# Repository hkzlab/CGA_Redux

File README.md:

# Color Graphics Adapter - Redux

## Introduction

The Color Graphics Adapter (**CGA**) Redux board is a more or less faithful clone of the original IBM CGA, based on the original schematics.

Since revision 0.2 of this board, **You can decide to build it with the "new" or "old" style composite output**, giving you slightly different colours.

Have a look [HERE](https://int10h.org/blog/2015/08/8088-mph-final-old-vs-new-cga-gory-details/) for a blog post that discusses the difference in regard to the famous **8088MPH** demo!

### Disclaimer

I take NO responsibility for what happens if you decide to build and use this card. Your computer might crash, catch fire or be destroyed in other nasty ways.
You're encourauged to take what you deem fit from this, and use it in your projects!

### Functionalities

✅ means I tested the functionality and it works, ❌ means I tested the functionality and found issues, ? means that the functionality has yet to be tested.

* [✅] Digital display in text mode, 40 columns
* [✅] Digital display in text mode, 80 columns
* [✅] Composite display in text mode, 40 columns
* [✅] Composite display in text mode, 80 columns
* [✅] Graphics mode in digital
* [✅] Graphics mode in composite
* [✅] Run CheckIt video test
* [✅] 8088MPH Demo
* [?] Light pen input

## Bill of Materials

| Component         | Qty | Type / Value        |
| ----------------- | --- | ------------------- |
| **TODO**          |     |                     |

### Character ROM

This board needs a character ROM to work. I would advise to search for a dump of IBM P/N 5788005, concatenate it four times and burn it on a 27C256 EPROM.

### Component substitutions

* U4,U5 and U101 should all be 'S174s, but I had only 'LS174 available. The board looks to be working without issues anyway
* U50-U57 are all 120ns DRAMs in my original board. I had only 150ns chips for this build, and they worked fine
* U9,U10 are 74153 chips. I tried to replace them with 74LS153 chips by Texas Instruments with good results. **Needs some testing with colored screens**
* U50-U57 can be substituted by 41256 / 4164 DRAMs like the M5K4164 or HM4864P (the additional address lines are grounded). **Tested with HM4864P**

## Support

If you wish to support me in building new hardware and software for old machines, [throw a few euros in my direction via Ko-Fi](https://ko-fi.com/hkzlab) ☕!

### 💰 Selling these boards 💰

I you want to contact me about selling this project, you can reach me via email at `0hkzUNDERSCOREprojects6ATposteoDOTnet` after properly fixing the email address by removing the digits and replacing the uppercase words with the proper characters.

**Contacts via other channels will be ignored**, as it means you did not read this document thoroughly.

"Collaborations" will boil down to the following:

- If you wish to produce and share this project at a loss or at cost, go for it. I am only asking for attribution and to let me know via email.
- If you want to do it for profit, let's discuss it. I'll probably settle for a rough 5% of the profit. Importing components is getting more expensive by the day, so this will contribute to me making future projects available for free.
- I will NOT do customer assistance for you or your customers. This is a hobby, not my job.

If this is not ok for you, you're cordially invited to go bother someone else :)

Authorized sellers will be listed in this README. If you find someone selling my boards without being listed here, it means they're stealing other people's work.

## Known issues

### Rev 0

* The Composite video out has an inverted connection for that type of footprint. (fixed in rev 0.1)
* Silkscreen for U28 says 74LS10, but it's actually an 74S10 on an original board (fixed in rev 0.1)
* traces that connect the edge to the power planes for 5V and GND are a bit too thin for my taste (fixed in rev 0.1)

## TODO

* ???

## Credits

Thanks to [Sergey Kiselev](https://github.com/skiselev) for his symbol/footprint library!

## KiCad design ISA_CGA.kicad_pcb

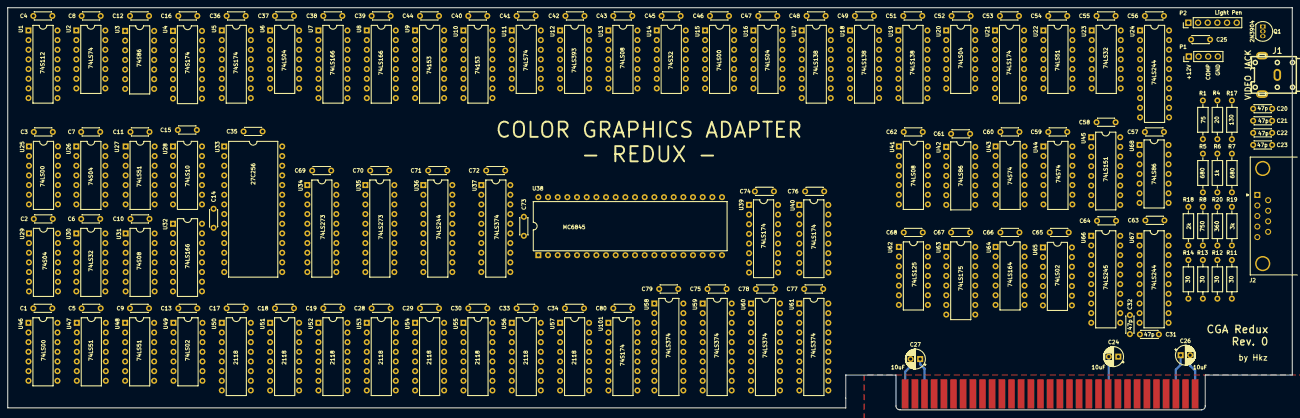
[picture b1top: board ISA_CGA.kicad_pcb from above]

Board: 4 copper layers, 337.6 x 105.7 mm, 168 parts (0 on the bottom side), 300 nets.

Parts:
C1, C2, C3, C4, C5, C6, C7, C8, C9, C10, C11, C12, C13, C14, C15, C16, C17, C18, C19, C25, C28, C29, C30, C33, C34, C35, C36, C37, C38, C39, C40, C41, C42, C43, C44, C45, C46, C47, C48, C49, C51, C52, C53, C54, C55, C56, C57, C58, C59, C60, C61, C62, C63, C64, C65, C66, C67, C68, C69, C70, C71, C72, C73, C74, C75, C76, C77, C78, C79, C80: 100nF; C_Disc_D4.3mm_W1.9mm_P5.00mm
C20, C21, C22, C23, C31, C32: 47p; C_Disc_D4.3mm_W1.9mm_P5.00mm
C24, C26, C27: 10uF; CP_Radial_D5.0mm_P2.50mm
J1: VIDEO JACK; rca_yellow
J2: RGBI Output; DSUB-9_Female_Horizontal_P2.77x2.84mm_EdgePinOffset7.70mm_H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
P1: 1X4 BERG; PinHeader_1x04_P2.54mm_Vertical
P2: 1X6 BERG; PinHeader_1x06_P2.54mm_Vertical
P5: Bus_ISA_8bit; Conn_Edge_PCB_ISA8
Q1: 2N3904; TO-92_Inline
R1: 75; R_Axial_DIN0207_L6.3mm_D2.5mm_P10.16mm_Horizontal
R4: 20; R_Axial_DIN0207_L6.3mm_D2.5mm_P10.16mm_Horizontal
R5, R7: 680; R_Axial_DIN0207_L6.3mm_D2.5mm_P10.16mm_Horizontal
R6: 1k; R_Axial_DIN0207_L6.3mm_D2.5mm_P10.16mm_Horizontal
R8: 750; R_Axial_DIN0207_L6.3mm_D2.5mm_P10.16mm_Horizontal
R11, R12, R13, R14: 30; R_Axial_DIN0207_L6.3mm_D2.5mm_P10.16mm_Horizontal
R17: 130; R_Axial_DIN0207_L6.3mm_D2.5mm_P10.16mm_Horizontal
R18: 2k; R_Axial_DIN0207_L6.3mm_D2.5mm_P10.16mm_Horizontal
R19: 3k; R_Axial_DIN0207_L6.3mm_D2.5mm_P10.16mm_Horizontal
R20: 360; R_Axial_DIN0207_L6.3mm_D2.5mm_P10.16mm_Horizontal
U1: 74S112; DIP-16_W7.62mm
U2, U11: 74LS74; DIP-14_W7.62mm
U3: 74S86; DIP-14_W7.62mm
U4, U5, U101: 74S174; DIP-16_W7.62mm
U6, U16, U20: 74LS04; DIP-14_W7.62mm
U7, U8, U32: 74LS166; DIP-16_W7.62mm
U9, U10: 74153; DIP-16_W7.62mm
U12: 74LS393; DIP-14_W7.62mm
U13, U41: 74LS08; DIP-14_W7.62mm
U14: 74S32; DIP-14_W7.62mm
U15, U25, U46: 74LS00; DIP-14_W7.62mm
U17, U18, U19: 74LS138; DIP-16_W7.62mm
U21, U39, U40: 74LS174; DIP-16_W7.62mm
U22, U27, U47, U48: 74LS51; DIP-14_W7.62mm
U23, U30: 74LS32; DIP-14_W7.62mm
U24, U36, U67: 74LS244; DIP-20_W7.62mm
U26, U29: 74S04; DIP-14_W7.62mm
U28: 74LS10; DIP-14_W7.62mm
U31: 74S08; DIP-14_W7.62mm
U33: 27C256; DIP-28_W15.24mm
U34, U35: 74LS273; DIP-20_W7.62mm
U37, U58, U59, U60, U61: 74LS374; DIP-20_W7.62mm
U38: MC6845; DIP-40_W15.24mm
U42, U68: 74LS86; DIP-14_W7.62mm
U43, U44: 74S74; DIP-14_W7.62mm
U45: 74LS151; DIP-16_W7.62mm
U49, U65: 74LS02; DIP-14_W7.62mm
U50, U51, U52, U53, U54, U55, U56, U57: 2118; DIP-16_W7.62mm
U62: 74LS125; DIP-14_W7.62mm
U63: 74LS175; DIP-16_W7.62mm
U64: 74LS164; DIP-14_W7.62mm
U66: 74LS245; DIP-20_W7.62mm

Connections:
3.58_MHZ: U5.12, U5.14, U43.12
14_MHZ: U1.1, U1.13, U4.9, U5.9, U6.13, U26.12, U43.11, U44.3
+12V: C24.1, C25.2, P1.1, P2.6, P5.9
/CGA 1/6/RAM-A0: U50.5, U51.5, U52.5, U53.5, U54.5, U55.5, U56.5, U57.5, U58.2, U59.2, U60.2, U61.2
/CGA 1/6/RAM-A1: U50.7, U51.7, U52.7, U53.7, U54.7, U55.7, U56.7, U57.7, U58.5, U59.5, U60.5, U61.5
/CGA 1/6/RAM-A2: U50.6, U51.6, U52.6, U53.6, U54.6, U55.6, U56.6, U57.6, U58.6, U59.6, U60.6, U61.6
/CGA 1/6/RAM-A3: U50.12, U51.12, U52.12, U53.12, U54.12, U55.12, U56.12, U57.12, U58.9, U59.9, U60.9, U61.9
/CGA 1/6/RAM-A4: U50.11, U51.11, U52.11, U53.11, U54.11, U55.11, U56.11, U57.11, U58.12, U59.12, U60.12, U61.12
/CGA 1/6/RAM-A5: U50.10, U51.10, U52.10, U53.10, U54.10, U55.10, U56.10, U57.10, U59.15, U60.15, U61.15, U62.3
/CGA 1/6/RAM-A6: U50.13, U51.13, U52.13, U53.13, U54.13, U55.13, U56.13, U57.13, U58.15, U59.16, U60.16, U61.16
/CGA 2/6/AT0: U7.2, U10.6, U35.19
/CGA 2/6/AT1: U8.2, U9.10, U35.16
/CGA 2/6/AT2: U7.3, U9.6, U35.15
/CGA 2/6/AT3: U8.3, U10.10, U35.12
/CGA 2/6/AT4: U7.4, U10.5, U35.9
/CGA 2/6/AT5: U8.4, U9.11, U35.6
/CGA 2/6/AT6: U7.5, U9.5, U35.5
/CGA 2/6/CC0: U7.10, U33.7, U34.19
/CGA 2/6/CC1: U8.10, U33.6, U34.16
/CGA 2/6/CC2: U7.11, U33.5, U34.15
/CGA 2/6/CC3: U8.11, U33.4, U34.12
/CGA 2/6/CC4: U7.12, U33.3, U34.9
/CGA 2/6/CC5: U8.12, U33.25, U34.6
/CGA 2/6/CC6: U7.14, U33.24, U34.5
/CGA 2/6/CC7: U8.14, U33.21, U34.2
/CGA 5/6/BLUE: U43.8, U45.3
/CGA 5/6/CYAN: U44.6, U45.1
/CGA 5/6/GREEN: U44.8, U45.2
/CGA 5/6/MAGENTA: U44.9, U45.14
/CGA 5/6/RED: U44.5, U44.12, U45.15
/CGA 5/6/YELLOW_BURST: U43.9, U44.2, U45.13
/CGA 6/6/DB0: P5.40, U66.2
/CGA 6/6/DB1: P5.39, U66.3
/CGA 6/6/DB2: P5.38, U66.4
/CGA 6/6/DB3: P5.37, U66.5
/CGA 6/6/DB4: P5.36, U66.6
/CGA 6/6/DB5: P5.35, U66.7
/CGA 6/6/DB6: P5.34, U66.8
/CGA 6/6/DB7: P5.33, U66.9
/CGA 6/6/OSC: P5.30, U26.13
/CGA 6/6/~SMEMR: P5.12, U42.12
A0: U13.6, U17.1, U38.24, U61.14
A1: P5.61, U17.2, U60.3
A2: P5.60, U17.3, U60.4
A3: P5.59, U17.6, U30.1, U60.7
A4: P5.58, U18.1, U60.8
A5: P5.57, U18.5, U60.13
A6: P5.56, U18.2, U60.14
A7: P5.55, U18.3, U60.17
A8: P5.54, U41.2, U61.3
A9: P5.53, U41.1, U61.4
A10: P5.52, U61.7
A11: P5.51, U61.8
A12: P5.50, U61.13
A13: P5.49, U61.17
A15: P5.47, U19.1
A16: P5.46, U19.2
A17: P5.45, U19.3
A18: P5.44, U19.4
A19: P5.43, U19.6
AEN: P5.42, U14.9, U18.4
ALPHA_DOTS: U14.6, U22.11
AT7: U8.5, U28.11, U31.9, U35.2
AT_LATCH: U35.11, U47.8
B: U45.11, U67.6, U67.15, U101.7
BACKGROUND_I: U10.12, U39.12
B_OUT: C22.1, R13.2, U67.14
C0: U7.13, U9.12, U22.2, U23.2, U48.2
C1: U8.13, U9.4, U23.1, U48.4
CAS_CC: U3.11, U25.10, U29.13
CC_LATCH: U25.8, U34.11
CHG_DOTS: U13.13, U32.13
COLOR_SEL: U22.4, U39.15
COMP_VID: J1.1, P1.3, R4.1
CURSOR: U20.1, U38.19
D0: U24.3, U36.2, U37.2, U38.33, U39.3, U40.3, U66.18
D1: U24.5, U36.4, U37.5, U38.32, U39.4, U40.4, U66.17
D2: U24.7, U36.6, U37.6, U38.31, U39.6, U40.6, U66.16
D3: U24.9, U36.8, U37.9, U38.30, U39.11, U40.11, U66.15
D4: U36.11, U37.12, U38.29, U39.13, U40.13, U66.14
D5: U36.13, U37.15, U38.28, U39.14, U40.14, U66.13
D6: U36.15, U37.16, U38.27, U66.12
D7: U36.17, U37.19, U38.26, U66.11
DATA_GATE: U13.8, U66.19
DISPEN: U20.3, U38.18
DOT_CLOCK: U7.7, U8.7, U25.2, U26.11, U27.8, U32.7
E: U11.9, U38.23
ENABLE_BLINK: U16.5, U28.10, U40.15
G: U24.4, U67.4, U68.1, U101.5
GND: C1.1, C2.1, C3.1, C4.1, C5.1, C6.1, C7.1, C8.1, C9.1, C10.1, C11.1, C12.1, C13.1, C14.1, C15.1, C16.1, C17.1, C18.1, C19.1, C20.2, C21.2, C22.2, C23.2, C24.2, C25.1, C26.2, C27.2, C28.1, C29.1, C30.1, C31.2, C32.2, C33.1, C34.1, C35.1, C36.1, C37.1, C38.1, C39.1, C40.1, C41.1, C42.1, C43.1, C44.1, C45.1, C46.1, C47.1, C48.1, C49.1, C51.1, C52.1, C53.1, C54.1, C55.1, C56.1, C57.1, C58.1, C59.1, C60.1, C61.1, C62.1, C63.1, C64.1, C65.1, C66.1, C67.1, C68.1, C69.1, C70.1, C71.1, C72.1, C73.1, C74.1, C75.1, C76.1, C77.1, C78.1, C79.1, C80.1, J1.2, J2.0, J2.1, J2.2, P1.4, P2.4, P5.1, P5.10, P5.31, R1.1, R17.2, U1.8, U2.7, U3.7, U4.8, U5.8, U6.7, U7.1, U7.6, U7.8, U8.1, U8.6, U8.8, U9.8, U10.8, U11.7, U12.7, U13.7, U14.7, U15.7, U16.7, U17.8, U18.8, U19.8, U20.7, U21.8, U22.7, U23.7, U24.1, U24.10, U25.7, U26.7, U27.7, U28.7, U29.7, U30.7, U31.7, U32.1, U32.6, U32.8, U33.2, U33.14, U33.22, U33.23, U33.26, U33.27, U34.10, U35.10, U36.10, U37.10, U38.1, U39.8, U40.8, U41.7, U42.7, U42.13, U43.7, U44.7, U45.4, U45.7, U45.8, U46.7, U47.7, U48.7, U49.7, U50.8, U51.8, U52.8, U53.8, U54.8, U55.8, U56.8, U57.8, U58.10, U59.10, U60.10, U61.10, U62.7, U62.10, U62.13, U63.8, U64.7, U65.7, U66.10, U67.1, U67.10, U67.19, U68.7, U101.8
GRPH: U16.11, U22.13, U23.13, U40.5, U47.1, U48.12
G_OUT: C21.1, R12.2, U67.16
HCLK: U5.7, U6.9, U21.9, U27.3
HRES: U16.13, U27.2, U27.9, U30.5, U40.2, U47.3, U49.3
HSYNC: U21.6, U38.39
HSYNC_DLY: U21.7, U43.1, U64.9, U65.6
HSYNC_OUT: C32.1, J2.8, U67.9
I: U24.6, U67.8, U101.10
IO_CLOCK: P5.20, U11.11
IO_READY: P5.41, U62.6
I_OUT: C23.1, R14.2, U67.12
LCLK: U6.2, U27.5, U43.3, U64.8
LPEN_STR: U11.5, U24.15, U38.3
MD0: U34.18, U35.18, U36.18, U37.3, U57.2, U57.14
MD1: U34.17, U35.17, U36.16, U37.4, U56.2, U56.14
MD2: U34.14, U35.14, U36.14, U37.7, U55.2, U55.14
MD3: U34.13, U35.13, U36.12, U37.8, U54.2, U54.14
MD4: U34.8, U35.8, U36.9, U37.13, U53.2, U53.14
MD5: U34.7, U35.7, U36.7, U37.14, U52.2, U52.14
MD6: U34.4, U35.4, U36.5, U37.17, U51.2, U51.14
MD7: U34.3, U35.3, U36.3, U37.18, U50.2, U50.14
MUX_A: U9.14, U10.14, U23.8
MUX_B: U9.2, U10.2, U23.11
unnamed: J2.3, R11.1
unnamed: J2.4, R12.1
unnamed: J2.5, R13.1
unnamed: J2.6, R14.1
unnamed: P5.62, U13.4, U13.5
unnamed: Q1.1, R1.2, R4.2
unnamed: Q1.2, R5.1, R6.1, R7.1, R8.1, R17.1, R18.1, R19.1, R20.2
unnamed: R5.2, U24.18
unnamed: R6.2, U24.16
unnamed: R7.2, U24.14
unnamed: R8.2, U24.12
unnamed: R18.2, U67.3
unnamed: R19.2, U67.5
unnamed: U1.5, U46.5, U46.13
unnamed: U1.6, U46.2, U46.10
unnamed: U1.9, U3.9
unnamed: U1.12, U26.4
unnamed: U2.6, U28.4, U47.2
unnamed: U2.10, U29.6
unnamed: U2.5, U2.12
unnamed: U2.4, U2.9, U2.13
unnamed: U3.1, U5.5, U6.11
unnamed: U3.3, U30.10
unnamed: U3.8, U31.1
unnamed: U3.12, U4.5, U4.6, U49.2
unnamed: U4.7, U4.11
unnamed: U4.15, U5.3
unnamed: U5.10, U6.5
unnamed: U5.13, U6.4
unnamed: U5.15, U6.3
unnamed: U10.7, U101.6
unnamed: U10.9, U101.11
unnamed: U10.11, U31.8
unnamed: U11.1, U17.12
unnamed: U11.3, U29.4
unnamed: U11.4, U17.11
unnamed: U11.12, U11.13, U15.8, U16.1
unnamed: U12.2, U12.12, U65.13
unnamed: U13.1, U15.3
unnamed: U13.9, U29.10
unnamed: U13.11, U14.4
unnamed: U13.12, U14.3
unnamed: U14.1, U28.8
unnamed: U14.5, U49.13
unnamed: U14.8, U41.4
unnamed: U14.11, U65.8
unnamed: U14.12, U20.10
unnamed: U14.13, U43.5
unnamed: U15.2, U21.5, U21.14
unnamed: U15.4, U15.5, U43.2, U64.13
unnamed: U15.6, U42.9
unnamed: U15.11, U28.1
unnamed: U15.12, U16.3, U40.12
unnamed: U16.2, U17.4, U65.3
unnamed: U16.4, U22.12, U23.5
unnamed: U16.9, U22.3, U29.9, U40.7
unnamed: U17.5, U18.7, U30.2, U65.2
unnamed: U18.6, U41.3
unnamed: U19.5, U41.11
unnamed: U20.2, U21.3
unnamed: U20.5, U22.6
unnamed: U20.11, U64.12
unnamed: U20.12, U24.2
unnamed: U20.13, U42.6
unnamed: U21.2, U21.13
unnamed: U22.1, U23.3
unnamed: U22.8, U23.9
unnamed: U23.4, U26.8
unnamed: U23.6, U28.13
unnamed: U24.8, U45.5
unnamed: U25.1, U25.11, U48.5
unnamed: U25.9, U30.6
unnamed: U25.3, U25.12, U48.3
unnamed: U25.13, U26.10
unnamed: U26.5, U46.9, U46.12, U47.6
unnamed: U26.6, U46.1, U46.4
unnamed: U26.9, U48.6
unnamed: U28.2, U65.4
unnamed: U28.3, U29.2
unnamed: U28.5, U49.4
unnamed: U29.11, U65.1
unnamed: U29.12, U31.2
unnamed: U30.9, U49.1
unnamed: U32.2, U33.11
unnamed: U32.3, U33.12
unnamed: U32.4, U33.13
unnamed: U32.5, U33.15
unnamed: U32.10, U33.16
unnamed: U32.11, U33.17
unnamed: U32.12, U33.18
unnamed: U32.14, U33.19
unnamed: U33.20, U68.11
unnamed: U38.4, U59.3
unnamed: U38.5, U59.4
unnamed: U38.6, U59.7
unnamed: U38.7, U59.8
unnamed: U38.8, U59.13
unnamed: U38.9, U59.14
unnamed: U38.10, U59.17
unnamed: U38.11, U58.3
unnamed: U38.12, U58.4
unnamed: U38.13, U58.7
unnamed: U38.14, U58.8
unnamed: U38.15, U58.13
unnamed: U38.16, U48.9
unnamed: U41.6, U66.1
unnamed: U41.8, U42.4, U67.13
unnamed: U41.9, U63.2, U63.5
unnamed: U41.10, U63.14
unnamed: U5.6, U42.3
unnamed: U42.5, U63.9, U64.4, U67.11
unnamed: U42.8, U64.1
unnamed: U42.10, U64.6
unnamed: U45.9, U68.6
unnamed: U45.10, U68.3
unnamed: U48.8, U49.8, U49.9
unnamed: U49.10, U58.14
unnamed: U62.8, U62.12
unnamed: U63.10, U63.13
unnamed: U63.7, U63.12
unnamed: U65.10, U68.2, U68.5
unnamed: U68.8, U68.12
unnamed: U9.7, U101.3
unnamed: U9.9, U101.4
unnamed: U101.12, U101.14
OVERSCAN_B: U10.3, U39.2
OVERSCAN_G: U9.13, U39.5
OVERSCAN_I: U10.13, U39.10
OVERSCAN_R: U9.3, U39.7
Q1: U2.3, U3.4, U5.2, U5.4, U47.4, U60.11, U61.11
Q4: U3.13, U4.10, U4.13, U42.2, U68.10
Q5: U1.11, U4.12, U4.14, U26.3, U49.6
R: U67.2, U67.17, U68.4, U101.2
RA0: U33.10, U38.38, U48.1
RA1: U33.9, U38.37
RA2: U33.8, U38.36
RAS: U1.3, U3.6, U26.1
RESET: P5.2, U20.9, U68.13
R_OUT: C20.1, R11.2, U67.18
SEL_BLUE: U10.4, U20.6
SL: U7.15, U8.15, U32.15, U62.11
SL': U30.8, U62.9
STR: U9.1, U9.15, U10.1, U10.15, U28.12
VCC: C1.2, C2.2, C3.2, C4.2, C5.2, C6.2, C7.2, C8.2, C9.2, C10.2, C11.2, C12.2, C13.2, C14.2, C15.2, C16.2, C17.2, C18.2, C19.2, C26.1, C27.1, C28.2, C29.2, C30.2, C33.2, C34.2, C35.2, C36.2, C37.2, C38.2, C39.2, C40.2, C41.2, C42.2, C43.2, C44.2, C45.2, C46.2, C47.2, C48.2, C49.2, C51.2, C52.2, C53.2, C54.2, C55.2, C56.2, C57.2, C58.2, C59.2, C60.2, C61.2, C62.2, C63.2, C64.2, C65.2, C66.2, C67.2, C68.2, C69.2, C70.2, C71.2, C72.2, C73.2, C74.2, C75.2, C76.2, C77.2, C78.2, C79.2, C80.2, P2.5, P5.3, P5.29, Q1.3, R20.1, U1.4, U1.10, U1.14, U1.15, U1.16, U2.1, U2.14, U3.14, U4.16, U5.16, U6.14, U7.16, U8.16, U9.16, U10.16, U11.2, U11.10, U11.14, U12.14, U13.14, U14.14, U15.14, U16.14, U17.16, U18.16, U19.16, U20.14, U21.1, U21.16, U22.9, U22.14, U23.14, U24.20, U25.14, U26.14, U27.10, U27.13, U27.14, U28.14, U29.14, U30.14, U31.14, U32.16, U33.1, U33.28, U34.1, U34.20, U35.20, U36.20, U37.20, U38.20, U39.16, U40.16, U41.14, U42.14, U43.14, U44.14, U45.12, U45.16, U46.14, U47.10, U47.13, U47.14, U48.10, U48.13, U48.14, U49.14, U50.16, U51.16, U52.16, U53.16, U54.16, U55.16, U56.16, U57.16, U58.20, U59.20, U60.20, U61.20, U62.14, U63.4, U63.16, U64.2, U64.14, U65.14, U66.20, U67.20, U68.14, U101.1, U101.16
VIDEO_ENABLE: U13.2, U40.10
VSYNC: U21.11, U38.40
VSYNC_DLY: U12.1, U21.10, U24.11, U63.1, U65.5, U65.9
VSYNC_OUT: C31.1, J2.9, U67.7
XACK: U2.8, U37.11, U62.5
~7_MHZ: U5.11, U6.6, U27.1
~14_MHZ: U6.12, U27.11, U44.11, U101.9
~6845_CS: U30.3, U38.25
~BLINK: U12.11, U14.2
~BW_1: U29.8, U44.1, U44.4, U44.10, U44.13
~BW_2: U16.8, U22.5, U43.4, U43.10, U43.13
~CAS: U31.3, U50.15, U51.15, U52.15, U53.15, U54.15, U55.15, U56.15, U57.15
~CCLK: U27.6, U30.4, U38.21, U47.11
~CLR_SR: U7.9, U8.9, U13.3, U32.9, U35.1
~CPU_MEM_SEL: U2.2, U13.10, U19.7, U29.5, U30.12, U62.4
~CURSOR_BLINK: U12.6, U12.13, U49.12
~CURSOR_DLY: U21.12, U28.9, U49.11
~DISPEN: U20.4, U21.4, U24.17
~DISPEN_DLY: U15.1, U15.13, U21.15, U23.10, U23.12
~ENABLE_BLINK: U16.6, U31.10
~EN_CPU_CAS_ADDR: U46.6, U61.1
~EN_CPU_RAS_ADDR: U46.3, U60.1
~EN_CRT_CAS_ADDR: U46.11, U58.1, U62.1
~EN_CRT_RAS_ADDR: U46.8, U59.1
~GRPH: U16.10, U22.10, U47.9, U48.11
~HCLK: U6.8, U62.2
~HRES: U16.12, U27.4, U27.12, U47.5
~IOR: P5.14, U14.10, U15.9
~IOW: P5.13, U15.10, U38.22
~LCLK: U3.2, U3.5, U3.10, U4.2, U4.4, U6.1, U68.9
~LPEN_INPUT: P2.1, U29.3
~LPEN_SW: P2.3, U24.13
~MEMR: U30.13, U41.5, U41.12, U42.11
~MEMW: P5.11, U29.1, U41.13
~Q2': U4.3, U6.10, U42.1, U47.12, U49.5
~RAS: U1.2, U2.11, U26.2, U50.4, U51.4, U52.4, U53.4, U54.4, U55.4, U56.4, U57.4, U58.11, U59.11
~RD_GATE: U30.11, U37.1
~RESET: U4.1, U5.1, U38.2, U39.1, U40.1, U101.15
~RESET': U20.8, U65.11, U65.12, U101.13
~SEL_1: U17.15, U40.9
~SEL_2: U17.14, U39.9
~STATUS_SEL: U17.13, U24.19
~WE: U28.6, U36.1, U36.19, U50.3, U51.3, U52.3, U53.3, U54.3, U55.3, U56.3, U57.3

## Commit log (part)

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2021-03-08 Add empty project
2021-03-08 Begin drawing first sheet of CGA
2021-03-08 Complete a sheet
2021-03-08 Remove char from label
2021-03-09 Begin 2nd sheet
2021-03-09 More drawings of sheet 2
2021-03-09 More sheet 2
2021-03-09 More sheet 2
2021-03-09 Move some components
2021-03-09 More of sheet 2
2021-03-10 Added MK36000 symbol
2021-03-10 More sheet 2 changes
2021-03-10 Resized sheet
2021-03-10 Added power for ICs in sheet 2
2021-03-10 Begin drawing sheet 3/6
2021-03-10 More sheet 3 drawing
2021-03-10 More sheet 3
2021-03-11 Sheet 3
2021-03-11 Cleanup more sheet 3
2021-03-11 Cleanup sheet
2021-03-11 Power connection for more units
2021-03-11 more sheets
2021-03-11 More power inputs
2021-03-11 Begin sheet 4
2021-03-11 More sheet 4
2021-03-11 More CGA sheet 4
2021-03-11 Some more sheet 4
2021-03-12 Add original manual
2021-03-12 Add more of sheet 4
2021-03-13 Sheet 4
2021-03-13 Begin sheet 5
2021-03-13 More sheet 5
2021-03-14 Sheet 5
2021-03-14 More power connections for sheet 5
2021-03-14 Add some components to sheet 6
2021-03-14 More sheet 6
2021-03-14 Sheet 6
2021-03-14 Add pics and readme
2021-03-14 Replace pic with PNG
2021-03-14 Add pic
2021-03-14 Update board
2021-03-15 Fix some label types in sheet 1
2021-03-15 Fix some more label types
2021-03-19 Add missing connection to Vcc/GND for two ICs
2021-03-20 Fix one of the gates of U15 on sheet 3
2021-03-20 Fixed some duplicate units and mislabeling
2021-03-20 Fix RAM bus connections
2021-03-20 Fix some more flags and footprints
2021-03-21 Cleanup schematics a bit
2021-03-25 Update note on caps at the RGBI connector
2021-03-25 Reorganize DRAM address lines
2021-03-25 Added note on RAM chips
2021-03-28 Add note on light pen input and change the label types
2021-03-29 Add extra libraries and assign footprints
2021-03-29 Replace MK36000 with 27C256
2021-03-29 Begin preparing board
2021-03-29 Fixed some footprints
2021-04-02 Add filter caps for every IC
2021-04-02 Begin laying out ICs
2021-04-02 Laying out more components
2021-04-02 Additional layout
2021-04-02 Reorganize space between ICs
2021-04-02 More layout
2021-04-02 Reorganize layout a bit
2021-04-02 Place some more ICs
2021-04-02 Place more components
2021-04-02 place all components
2021-04-02 Add mask
2021-04-02 Close board outline
2021-04-02 Changed footprints, moving components
2021-04-02 Redone layout
2021-04-02 Route power tracks in inner layers
2021-04-02 Moved some components
2021-04-02 Add keepout areas for autorouter
2021-04-02 Added copper fill zones
2021-04-03 Fix connections in power plane
2021-04-03 Added some silkscreen
2021-04-03 Add some more silkscreen entries
2021-04-03 More silkscreen, slightly move component
2021-04-03 More silkscreen
2021-04-04 Commit PCB before importing the routed traces
2021-04-04 Imported traces
2021-04-06 Remove redundant file
2021-04-07 Fixed wrong DRAM pinout
2021-04-07 connect the two NC in DRAM to GND, so ideally 4164 and 41256 can be used
2021-04-19 Rewire 27C256 so a dump from the original MK36000 can be used unchanged
2021-04-27 Reroute tracks to edge connector
2021-04-27 Reroute backside traces to edge connector
2021-04-27 Fix back mask
2021-04-27 Reroute some tracks that were in inner layers
2021-05-25 Add some more grounding
2021-05-27 Add rev 1.0 gerbers
2021-05-28 Add fatter power traces, added gerbers for rev.0
2021-05-28 Slightly move a via
2021-06-09 Replaced RCA jack
2021-06-10 Fix power trace running below composite connector
2021-06-10 Replaced 74LS10 for U28 with 74S10
2021-06-10 Add new README
2021-06-10 Update to the README
2021-06-10 Fix missing end of sentence in README
2021-06-10 Add section on functionalities
2021-06-12 Add more positive checks to the README!
2021-06-12 Updated README with note on 8088MPH
2021-06-12 Clearup
2021-06-13 Add rev 0.1 gerbers, further noted in readme
2021-06-13 Updated the README
2021-06-13 Begin working on rev 0.2, for an easier "old" composite out mod
2021-06-13 Added silkscreen to tick the type of composite build
2021-06-13 Refilled copper zones
2021-06-13 Update 8088MPH test
2021-06-15 Add "old" Composite mod values to silkscreen on back
2021-06-17 Renamed components, cleaned the silkscreen
2021-06-17 Generate gerbers for rev 0.2
2021-07-04 Removed rev. 0.1 as superseded and never tested
2021-07-04 Add paragraph in README
2021-07-14 Additional notes on readme
2021-07-14 Additional notes
2021-11-09 Update KiCad url
2022-10-26 Add datasheet with information about the bracket
2023-10-13 Initial import of the board in Kicad 7
2023-10-13 Fix some junctions
2023-10-13 Update copper to edge constraint
2024-08-01 Remove backups by kicad...
2026-06-20 Fix Q1' naming thanks to Michael Karcher
